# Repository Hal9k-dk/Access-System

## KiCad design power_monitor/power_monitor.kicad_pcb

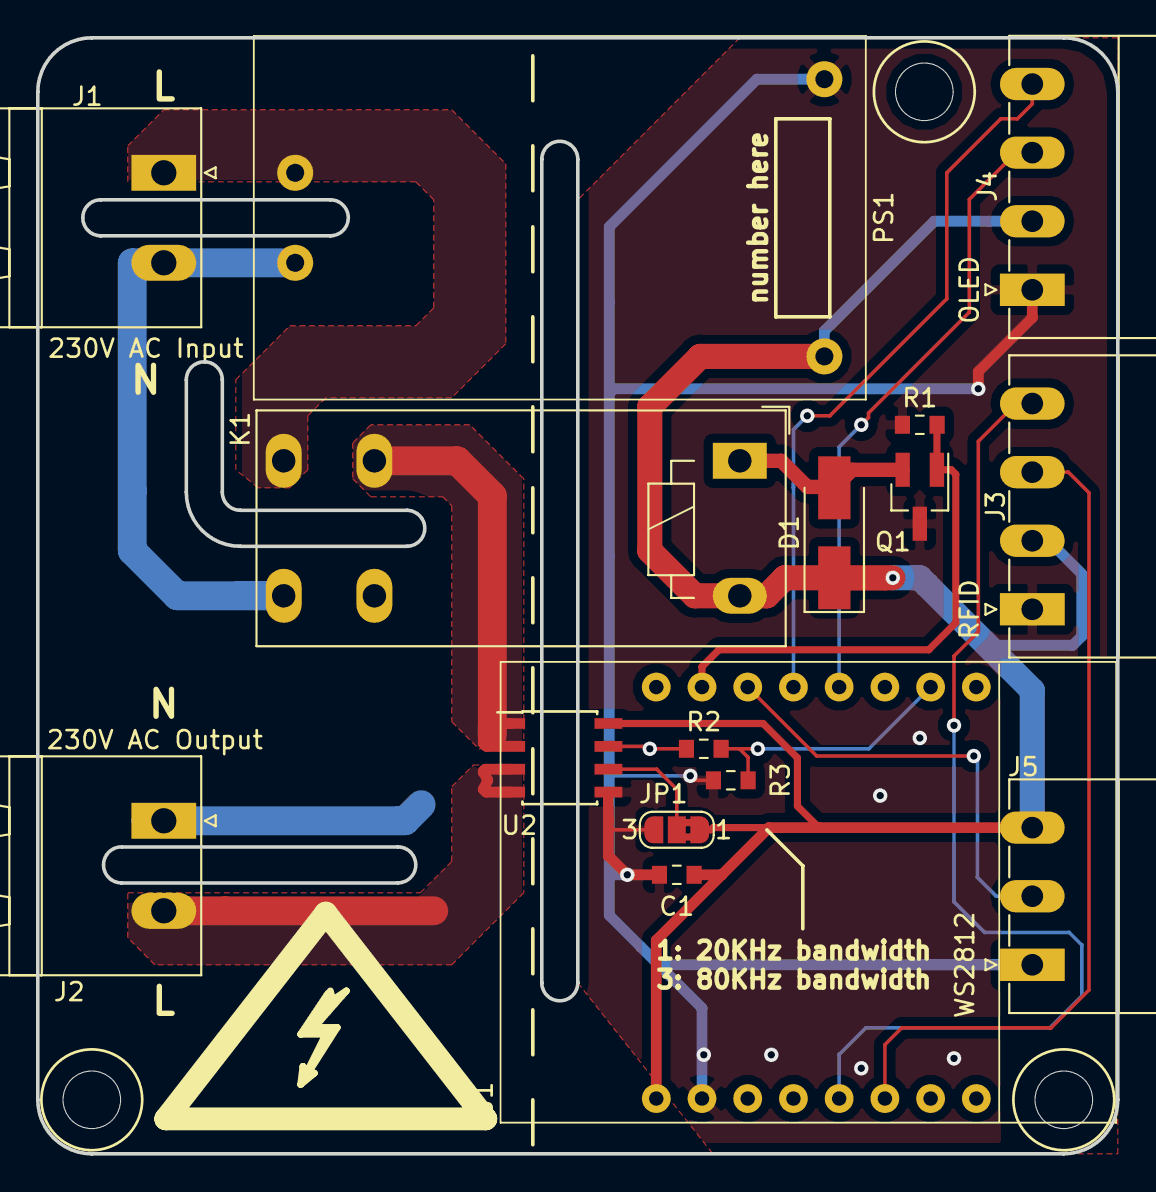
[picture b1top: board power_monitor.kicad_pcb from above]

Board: 2 copper layers, 60.0 x 62.0 mm, 16 parts (0 on the bottom side), 17 nets.

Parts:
C1: 0.1uF; C_0603_1608Metric_Pad0.84x1.00mm_HandSolder
D1: 1N4001; D_SMA_Handsoldering
J1: 230V AC Input; PhoenixContact_MSTBA_2,5_2-G_1x02_P5.00mm_Horizontal
J2: 230V AC Output; PhoenixContact_MSTBA_2,5_2-G_1x02_P5.00mm_Horizontal
J3: RFID; PhoenixContact_MC_1,5_4-G-3.81_1x04_P3.81mm_Horizontal
J4: OLED; PhoenixContact_MC_1,5_4-G-3.81_1x04_P3.81mm_Horizontal
J5: WS2812; PhoenixContact_MC_1,5_3-G-3.81_1x03_P3.81mm_Horizontal
JP1: BW_SEL; SolderJumper-3_P1.3mm_Bridged2Bar12_RoundedPad1.0x1.5mm_Num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
K1: G2RL-2A-DC5; Relay_DPST_Schrack-RT2-FormA_RM5mm
PS1: HLK-PM01
Q1: FDN339AN; SOT-23_Handsoldering
R1: 15k; R_0603_1608Metric_Pad0.84x1.00mm_HandSolder
R2: 6K8; R_0603_1608Metric_Pad0.84x1.00mm_HandSolder
R3: 15K; R_0603_1608Metric_Pad0.84x1.00mm_HandSolder
U1: Wemos-D1-mini; Wemos D1 Mini
U2: ACS723xMATR-10AB; SOIC-8_3.9x4.9mm_P1.27mm

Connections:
+5V: C1.2, D1.1, J3.2, J4.2, J5.3, JP1.1, K1.A2, PS1.4, U1.9, U2.8
/Power Handling/AC_L: J1.1, K1.14, PS1.1
/Power Handling/AC_L_Switched: J2.2, U2.3, U2.4
/Power Handling/AC_N: J1.2, K1.24, PS1.2
/Power Handling/AC_N_Switched: J2.1, K1.21
GND: C1.1, J3.1, J4.1, J5.1, JP1.3, PS1.3, Q1.3, R1.2, R3.2, U1.10, U2.5
unnamed: D1.2, K1.A1, Q1.2
unnamed: JP1.2, U2.6
unnamed: K1.11, U2.1, U2.2
unnamed: R2.2, R3.1, U1.2
RFID: J4.3, U1.4
RFID_SW: J4.4, U1.5
Relay: Q1.1, R1.1, U1.7
SCL: J3.3, U1.14
SDA: J3.4, U1.13
VIsense: R2.1, U2.7
WS2812: J5.2, U1.6

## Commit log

2018-04-08 Added renders and readme
2018-04-08 Added pdf of schematics
2018-04-08 Resized images
2018-04-08 removed images to refresh github
2018-04-08 re-added images to refresh github
2018-04-08 Added gerbers
2018-04-08 updated plot settings
2018-04-09 Reworked isolation, pours and silkscreen
2018-04-09 Re-poured pours to make sure
2018-04-09 Added case 3D models
2018-04-09 Fixed readme to propper image link
2018-04-09 Fixed relative link
2018-04-10 changed diode footprint
2018-04-12 Moved live in connector a bit
2018-04-16 Added 3D models of plugs
